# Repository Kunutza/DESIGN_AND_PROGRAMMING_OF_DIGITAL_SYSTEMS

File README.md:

Light and temperature detection for a safe.

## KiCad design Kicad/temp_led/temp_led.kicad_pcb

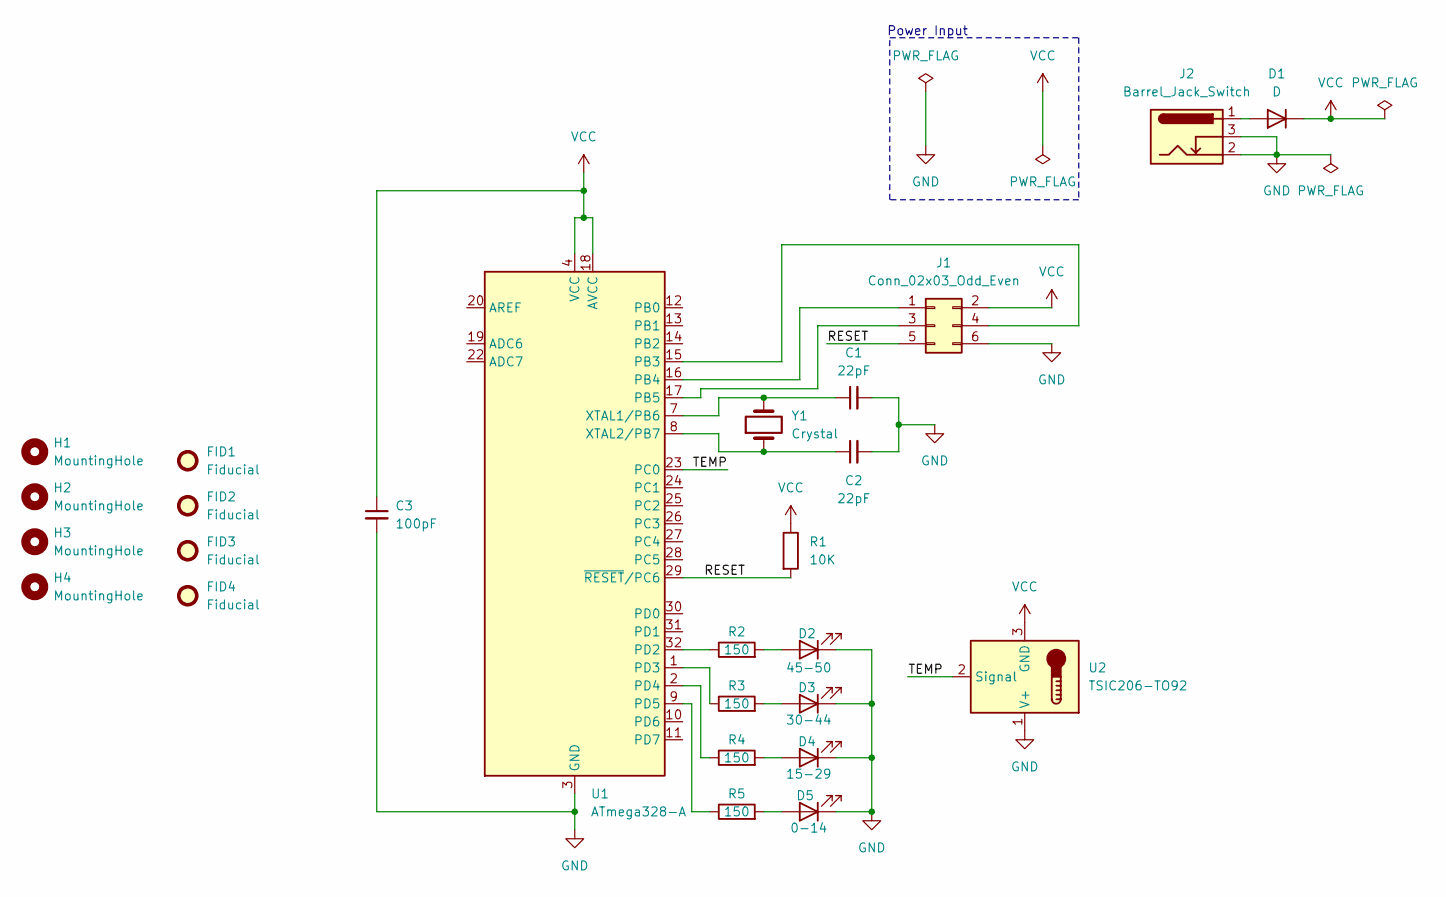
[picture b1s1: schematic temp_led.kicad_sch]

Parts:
C1, C2: 22pF; C_0805_2012Metric
C3: 100pF; C_0805_2012Metric
D1: D; D_1206_3216Metric
D2: 45-50; LED_D5.0mm
D3: 30-44; LED_D5.0mm
D4: 15-29; LED_D5.0mm
D5: 0-14; LED_D5.0mm
FID1, FID2, FID3, FID4: Fiducial; Fiducial_1mm_Mask2mm
H1, H2, H3, H4: MountingHole; MountingHole_3.2mm_M3
J1: Conn_02x03_Odd_Even; PinHeader_2x03_P2.54mm_Vertical
J2: Barrel_Jack_Switch; BarrelJack_Horizontal
R1: 10K; R_0805_2012Metric
R2, R3, R4, R5: 150; R_0805_2012Metric
U1: ATmega328-A; TQFP-32_7x7mm_P0.8mm
U2: TSIC206-TO92; TO-92_Inline
Y1: Crystal; Crystal_HC49-4H_Vertical

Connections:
/RESET: J1.5, R1.2, U1.29 (~RESET/PC6)
/TEMP: U1.23 (PC0), U2.2 (Signal)
GND: C1.2, C2.2, C3.2, D2.1 (K), D3.1 (K), D4.1 (K), D5.1 (K), J1.6, J2.2, J2.3, U1.3 (GND), U1.5 (GND), U1.21 (GND), U2.1 (V+)
unnamed: D1.2 (A), J2.1
unnamed: D2.2 (A), R2.2
unnamed: D3.2 (A), R3.2
unnamed: D4.2 (A), R4.2
unnamed: D5.2 (A), R5.2
unnamed: J1.1, U1.16 (PB4)
unnamed: J1.3, U1.17 (PB5)
unnamed: J1.4, U1.15 (PB3)
unnamed: R2.1, U1.32 (PD2)
unnamed: R3.1, U1.1 (PD3)
unnamed: R4.1, U1.2 (PD4)
unnamed: R5.1, U1.9 (PD5)
unnamed: C1.1, U1.7 (XTAL1/PB6), Y1.2
unnamed: C2.1, U1.8 (XTAL2/PB7), Y1.1
VCC: C3.1, D1.1 (K), J1.2, R1.1, U1.4 (VCC), U1.6 (VCC), U1.18 (AVCC), U2.3 (GND)

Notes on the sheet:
Power Input

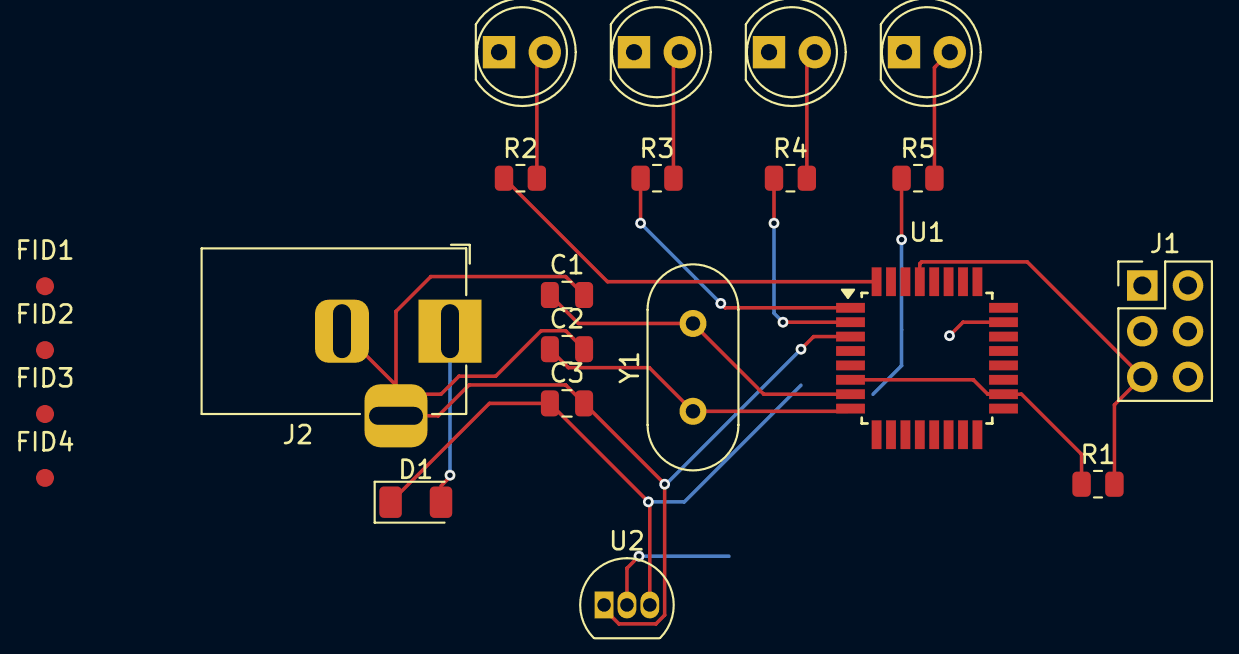
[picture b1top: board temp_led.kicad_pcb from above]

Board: 2 copper layers, 26 parts (0 on the bottom side), 18 nets.

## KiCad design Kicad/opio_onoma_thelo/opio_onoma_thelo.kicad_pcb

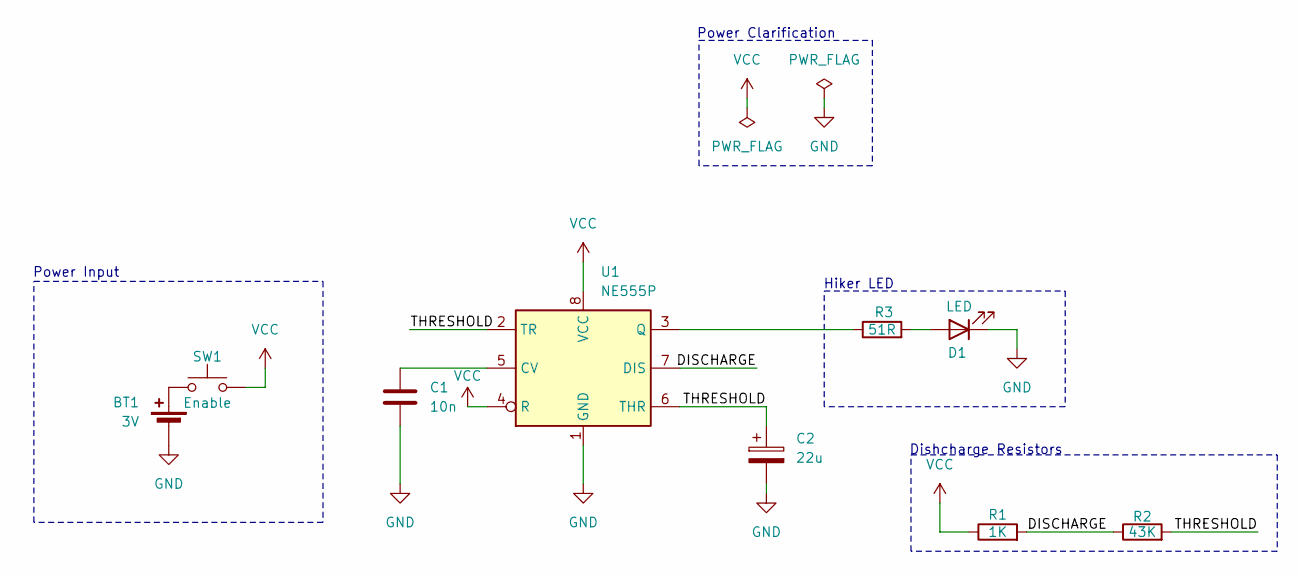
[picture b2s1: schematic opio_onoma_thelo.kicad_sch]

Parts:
BT1: 3V; BatteryHolder_Keystone_103_1x20mm
C1: 10n; C_Disc_D6.0mm_W4.4mm_P5.00mm
C2: 22u; C_Radial_D6.3mm_H5.0mm_P2.50mm
D1: LED; LED_D5.0mm_Clear
R1: 1K; R_Axial_DIN0207_L6.3mm_D2.5mm_P10.16mm_Horizontal
R2: 43K; R_Axial_DIN0207_L6.3mm_D2.5mm_P10.16mm_Horizontal
R3: 51R; R_Axial_DIN0207_L6.3mm_D2.5mm_P10.16mm_Horizontal
SW1: Enable; SW_PUSH_6mm_H5mm
U1: NE555P; DIP-8_W7.62mm

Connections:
/DISCHARGE: R1.2, R2.1, U1.7 (DIS)
/THRESHOLD: C2.1, R2.2, U1.2 (TR), U1.6 (THR)
GND: BT1.2 (-), C1.2, C2.2, D1.1 (K), U1.1 (GND)
unnamed: BT1.1 (+), SW1.1
unnamed: D1.2 (A), R3.2
unnamed: C1.1, U1.5 (CV)
unnamed: R3.1, U1.3 (Q)
VCC: R1.1, SW1.2, U1.4 (R), U1.8 (VCC)

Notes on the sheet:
Power Input
Power Clarification
Hiker LED
Dishcharge Resistors

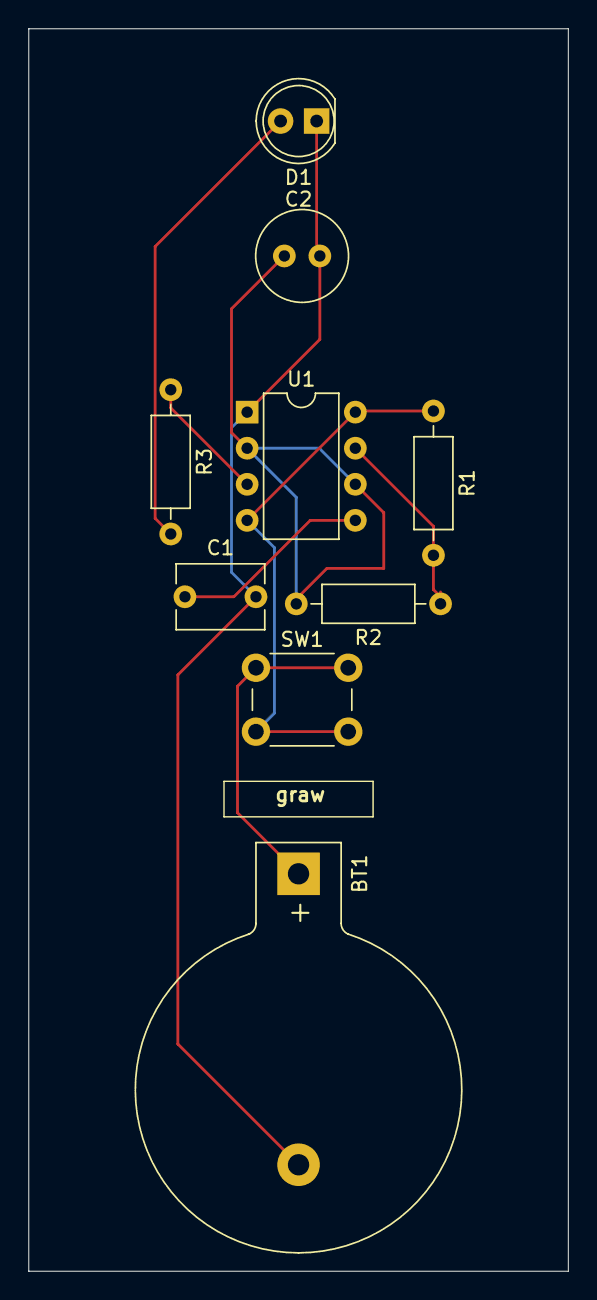
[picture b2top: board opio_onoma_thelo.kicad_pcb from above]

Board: 2 copper layers, 38.0 x 87.5 mm, 9 parts (0 on the bottom side), 8 nets.

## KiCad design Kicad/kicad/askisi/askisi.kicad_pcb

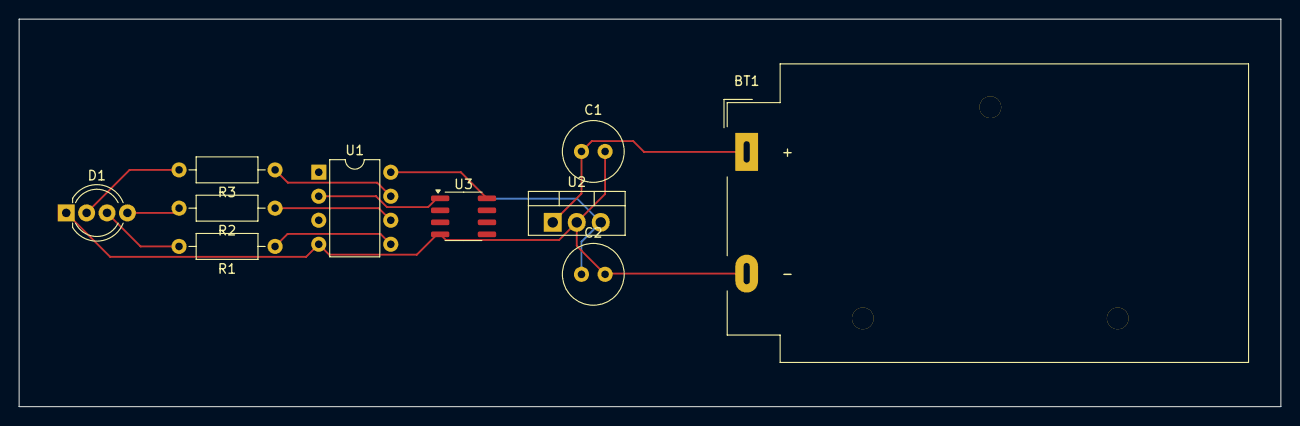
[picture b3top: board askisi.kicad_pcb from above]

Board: 2 copper layers, 133.5 x 41.0 mm, 10 parts (0 on the bottom side), 10 nets.

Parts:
BT1: 9V; BatteryHolder_MPD_BA9VPC_1xPP3
C1, C2: 22u; C_Radial_D6.3mm_H5.0mm_P2.50mm
D1: LED_RGB; LED_D5.0mm-4_RGB_Wide_Pins
R1, R2, R3: 220; R_Axial_DIN0207_L6.3mm_D2.5mm_P10.16mm_Horizontal
U1: ATtiny25-20P; DIP-8_W7.62mm
U2: LM7805_TO220; TO-220-3_Vertical
U3: TMP36xS; SOIC-8_3.9x4.9mm_P1.27mm

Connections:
/TEMP SENSOR: U1.2 (XTAL1/PB3), U3.1 (V_{OUT})
GND: BT1.2 (-), C1.2, C2.2, D1.1 (RK), U1.4 (GND), U2.2 (GND), U3.4 (GND)
unnamed: BT1.1 (+), C1.1, U2.1 (VI)
unnamed: D1.4 (BA), R2.2
unnamed: D1.5 (GA), R1.2
unnamed: D1.6 (RA), R3.2
unnamed: R1.1, U1.5 (AREF/PB0)
unnamed: R2.1, U1.6 (PB1)
unnamed: R3.1, U1.7 (PB2)
VCC: C2.1, U1.8 (VCC), U2.3 (VO), U3.8 (+Vs)

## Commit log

2025-04-16 batman
